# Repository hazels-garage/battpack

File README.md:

# batt!pack
A 'backpack' for the nice!nano to make wiring up a battery cleaner on boards without native support

### Bill of Materials
- [1x MSK-12C02](https://www.aliexpress.us/item/2251832670227688.html)

_image by sumandrew on discord_

#### Notes
I lost the source files for the most recent version, but do have the gerbers.  Make sure you're downloading `GERBER-battpack-2.zip` for the latest version.

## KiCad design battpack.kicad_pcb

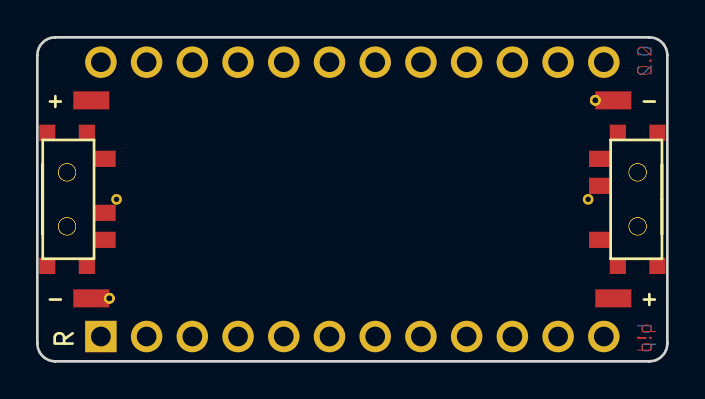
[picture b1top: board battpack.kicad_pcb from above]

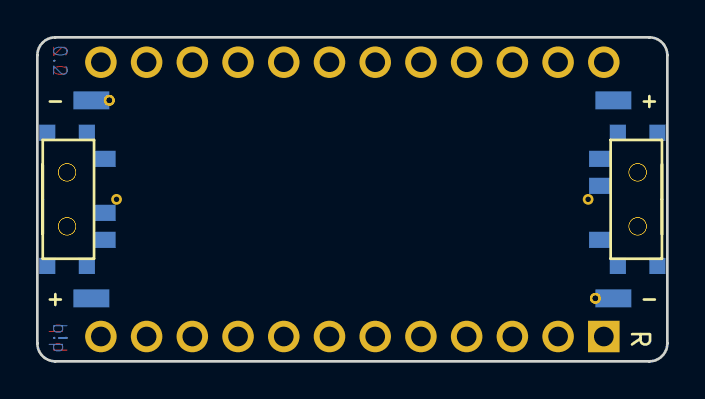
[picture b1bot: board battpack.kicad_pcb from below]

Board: 2 copper layers, 35.0 x 18.0 mm, 12 parts (2 on the bottom side), 3 nets, no tracks yet.

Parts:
PAD1, PAD2, PAD3, PAD4, PAD5, PAD6, PAD7, PAD8: SMDPad
T1, T2, T3, T4: SPDT_C128955

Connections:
BAT: PAD1.1, PAD3.1, PAD5.1, PAD7.1, T1.1, T2.1, T3.1, T4.1
GND: PAD2.1, PAD4.1, PAD6.1, PAD8.1
RAW: T1.2, T2.2, T3.2, T4.2

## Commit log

2022-10-25 init
2022-10-25 fix battery silks
2022-10-25 Initial double ended BattPack
2022-10-25 Reduced size of PCB at original end in order to not overhand OLED pin locations on existing boards
2022-10-26 rearrange
2022-10-26 rev2 init
2022-10-26 0.2 gerber
2022-10-26 why render not show?
2022-10-26 remove fill zone
2022-10-26 re-re-render
2022-10-27 update name
2022-10-27 add license to readme
2024-07-10 adding gerbers for v2
2026-03-26 remove link to site

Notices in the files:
README.md:
https://img.shields.io/github/license/hazels-garage/satpad?label=%20&logo=creativecommons&logoColor=%23ffffff&style=flat-square
